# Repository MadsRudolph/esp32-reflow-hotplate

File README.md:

# ESP32 SMD Reflow Hotplate

A from-scratch SMD reflow hotplate built around an ESP32, a 24 V DC PTC heater plate,
and a custom CNC-milled single-sided control board. Designed to reflow small/medium
SMD boards (up to ~100 × 100 mm) using PID-controlled reflow profiles.

> **Status:** in design. See [`docs/`](docs/) for the design spec.

## Why DC PTC (not mains)

The heater runs on **24 V DC**, switched by a power MOSFET — no mains voltage anywhere
in the build. Safer to build, debug, and leave running than an SSR + AC element.

## System overview

| Subsystem | Choice |
|---|---|
| Controller | ESP32 DevKit module |
| Heater | 24 V DC PTC aluminium plate, ~300 W (~13 A) |
| Power switch | IRFS4710 N-MOSFET, 12 V gate drive |
| Temp sensing | K-type thermocouple + MAX31855 (SPI) |
| Logic supply | 24 V → 5 V via LM2576 switching regulator |
| Gate-drive supply | 24 V → 12 V via LM7812 |
| UI | SSD1306 OLED + rotary encoder + start/stop button |
| Control board | Single-sided, through-hole, CNC-milled (Roland SRM-20) |
| Enclosure | 3D-printed (offset electronics box + metal-standoff plate mount) |

Most passives, the MOSFET, regulators, connectors and the encoder come from the **DTU
component shop** (through-hole lab stock). The ESP32 DevKit, MAX31855 thermocouple
module, OLED, 24 V PSU and the PTC heater plate are external modules/hardware.

## Repository layout

```
docs/            design spec, BOM, sourcing notes
hardware/kicad/   KiCad 10 project (schematic + single-sided board)
hardware/3d/      Blender sources + exported STL/STEP for printing
firmware/         ESP32 reflow-control firmware
```

## Production

- **PCB:** CNC-milled on a Roland SRM-20 (FR-1), single-sided, top nets as wire bridges.
  Design rules match the DTU laser/mill process: 1.0 mm trace / 0.8 mm clearance.
- **Enclosure:** FDM 3D print. The hot-plate mount uses **metal standoffs** with an air
  gap from the plastic — the plate reaches ~250 °C and must never touch printed parts.

## Safety

Mains-free by design, but reflow temperatures are dangerous. Planned protections:
hardware gate pulldown (power-off = heater-off), an inline thermal cutoff fuse on the
heater, a fused 24 V input, and firmware thermal-runaway / over-temperature watchdogs.

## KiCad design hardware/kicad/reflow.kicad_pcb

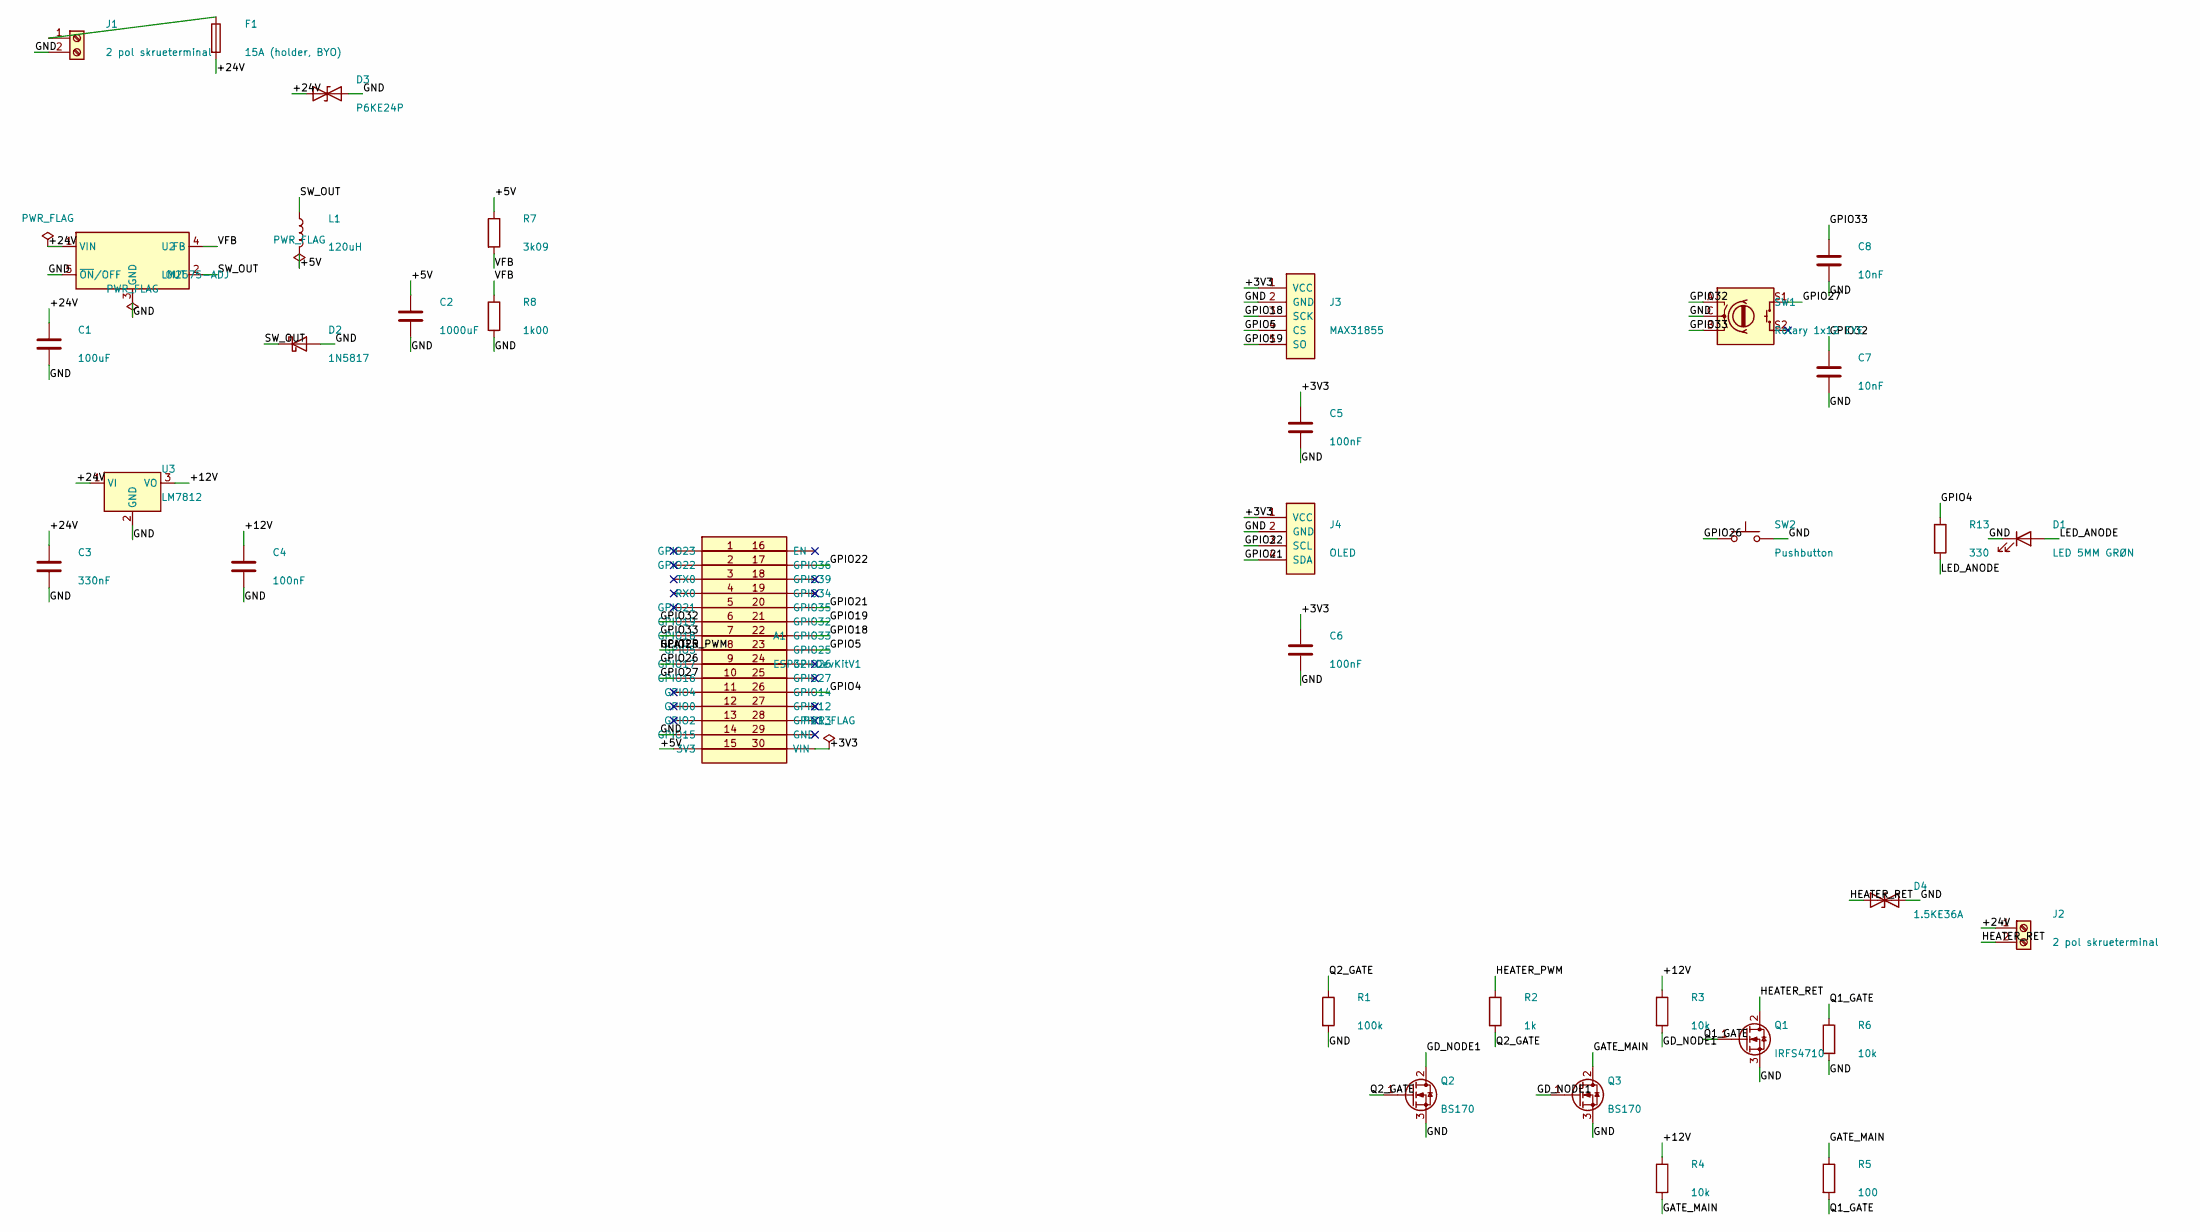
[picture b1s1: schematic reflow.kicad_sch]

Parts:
A1: ESP32-DevKitV1; ESP32_DevKitV1_2x15_P2.54_W22.86
C1: 100uF; CP_Radial_D8.0mm_P3.50mm
C2: 1000uF; CP_Radial_D10.0mm_P5.00mm
C3: 330nF; C_Disc_D5.0mm_W2.5mm_P2.50mm
C4, C5, C6: 100nF; C_Disc_D5.0mm_W2.5mm_P2.50mm
C7, C8: 10nF; C_Disc_D5.0mm_W2.5mm_P2.50mm
D1: LED 5MM GRØN; LED_D5.0mm
D2: 1N5817; D_DO-41_SOD81_P10.16mm_Horizontal
D3: P6KE24P; D_DO-201AD_P15.24mm_Horizontal
D4: 1.5KE36A; D_DO-201AD_P15.24mm_Horizontal
F1: 15A (holder, BYO); Fuseholder_Cylinder-5x20mm_Schurter_FUP_0031.2510_Horizonta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
J1, J2: 2 pol skrueterminal; TerminalBlock_bornier-2_P5.08mm
J3: MAX31855; Header_1x05_P2.54
J4: OLED; Header_1x04_P2.54
L1: 120uH; L_Toroid_Vertical_L26.7mm_W14.0mm_P10.16mm_Pulse_D
Q1: IRFS4710; TO-220-3_Vertical_LaserPads
Q2, Q3: BS170; TO-92_Inline_GDS
R1: 100k; R_Axial_DIN0207_L6.3mm_D2.5mm_P7.62mm_Horizontal
R2: 1k; R_Axial_DIN0207_L6.3mm_D2.5mm_P7.62mm_Horizontal
R3, R4, R6: 10k; R_Axial_DIN0207_L6.3mm_D2.5mm_P7.62mm_Horizontal
R5: 100; R_Axial_DIN0207_L6.3mm_D2.5mm_P7.62mm_Horizontal
R7: 3k09; R_Axial_DIN0207_L6.3mm_D2.5mm_P7.62mm_Horizontal
R8: 1k00; R_Axial_DIN0207_L6.3mm_D2.5mm_P7.62mm_Horizontal
R13: 330; R_Axial_DIN0207_L6.3mm_D2.5mm_P7.62mm_Horizontal
SW1: Rotary 1x12 EYE; RotaryEncoder_Alps_EC11E-Switch_Vertical_H20mm
SW2: Pushbutton; SW_PUSH_6mm
U2: LM2575-ADJ; TO-220-5_Vertical_LaserPads
U3: LM7812; TO-220-3_Vertical_LaserPads

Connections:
/+3V3: A1.30 (3V3), C5.1, C6.1, J3.1 (VCC), J4.1 (VCC)
/+5V: A1.15 (VIN), C2.1, L1.2, R7.1
/+12V: C4.1, R3.1, R4.1, U3.3 (VO)
/+24V: C1.1, C3.1, D3.1 (A1), F1.2, J2.1, U2.1 (VIN), U3.1 (VI)
/GATE_MAIN: Q3.2 (D), R4.2, R5.1
/GD_NODE1: Q2.2 (D), Q3.1 (G), R3.2
/GND: A1.14 (GND), C1.2, C2.2, C3.2, C4.2, C5.2, C6.2, C7.2, C8.2, D1.1 (K), D2.2 (A), D3.2 (A2), D4.2 (A2), J1.2, J3.2 (GND), J4.2 (GND), Q1.3 (S), Q2.3 (S), Q3.3 (S), R1.2, R6.2, R8.2, SW1.C, SW2.2, U2.3 (GND), U2.5 (~ON/OFF), U3.2 (GND)
/GPIO4: A1.26 (GPIO4), R13.1
/GPIO5: A1.23 (GPIO5), J3.4 (CS)
/GPIO18: A1.22 (GPIO18), J3.3 (SCK)
/GPIO19: A1.21 (GPIO19), J3.5 (SO)
/GPIO21: A1.20 (GPIO21), J4.4 (SDA)
/GPIO22: A1.17 (GPIO22), J4.3 (SCL)
/GPIO25: A1.8 (GPIO25), R2.1
/GPIO26: A1.9 (GPIO26), SW2.1
/GPIO27: A1.10 (GPIO27), SW1.S1
/GPIO32: A1.6 (GPIO32), C7.1, SW1.A
/GPIO33: A1.7 (GPIO33), C8.1, SW1.B
/HEATER_RET: D4.1 (A1), J2.2, Q1.2 (D)
/LED_ANODE: D1.2 (A), R13.2
/Q1_GATE: Q1.1 (G), R5.2, R6.1
/Q2_GATE: Q2.1 (G), R1.1, R2.2
/SW_OUT: D2.1 (K), L1.1, U2.2 (OUT)
/VFB: R7.2, R8.1, U2.4 (FB)
unnamed: F1.1, J1.1

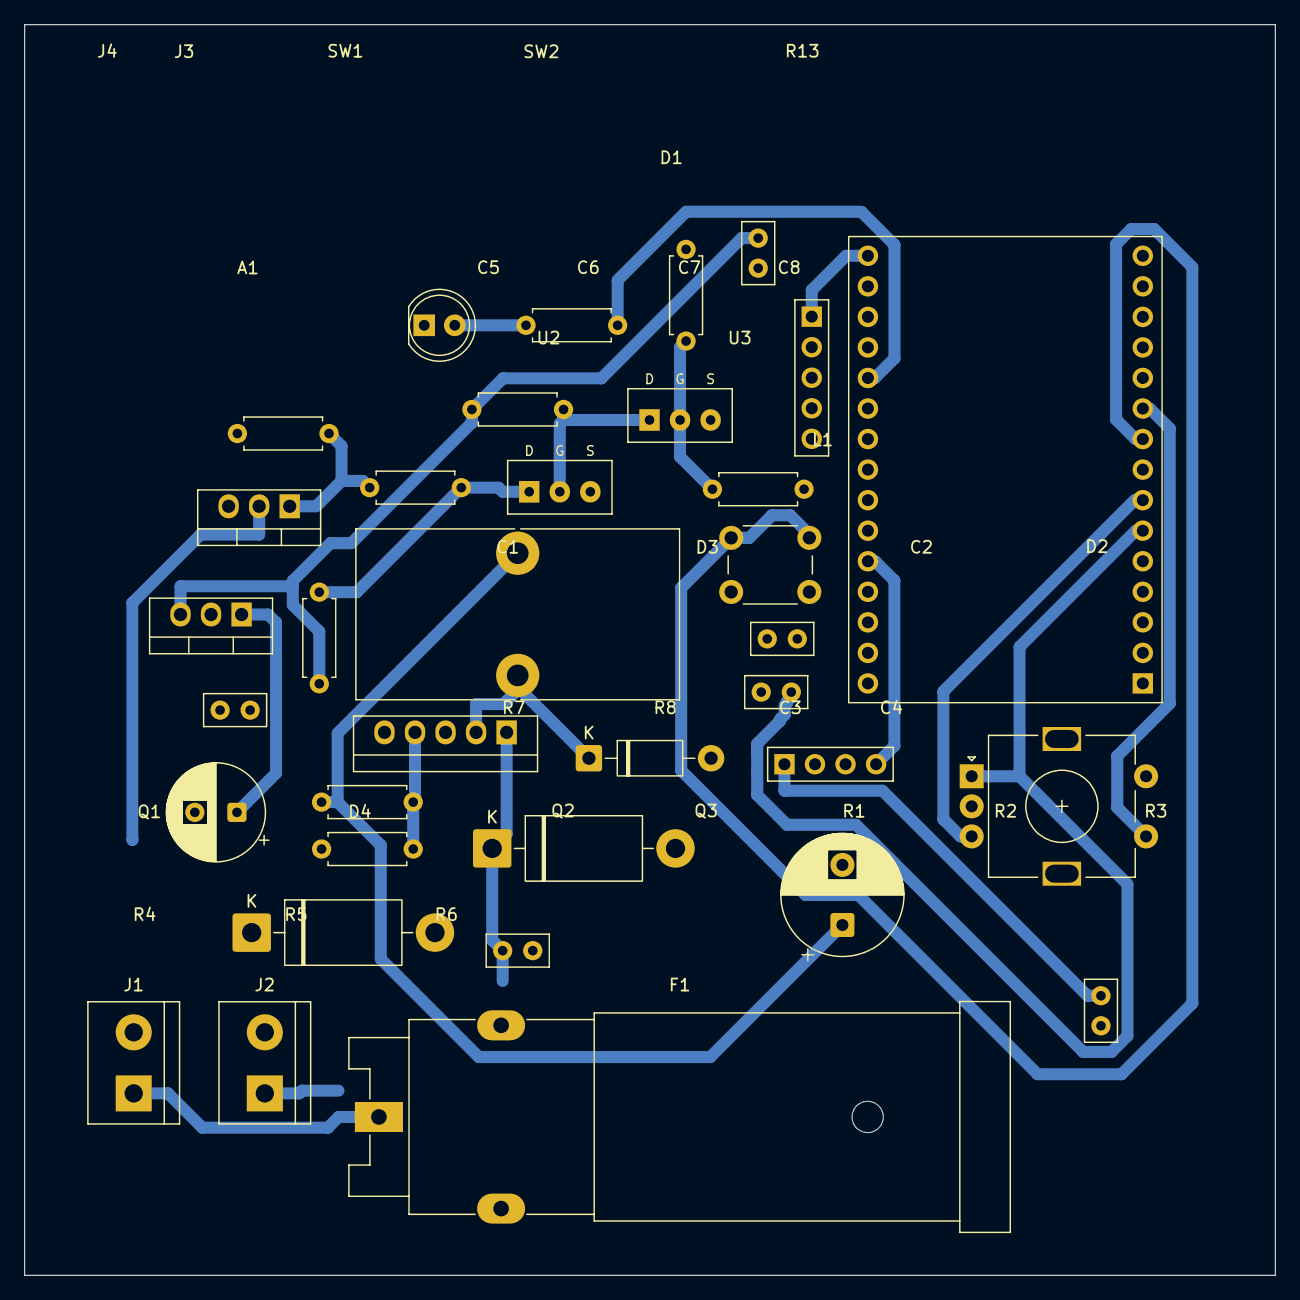
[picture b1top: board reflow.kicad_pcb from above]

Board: 2 copper layers, 104.0 x 104.0 mm, 35 parts (0 on the bottom side), 25 nets.

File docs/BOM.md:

# Bill of Materials — ESP32 reflow hotplate

> Generated from `hardware/kicad/reflow.kicad_sch` (the schematic is
> produced by `hardware/kicad/tools/build_schematic.py`). Every
> **board-soldered** line below resolves to a row in the DTU component
> shop catalogue (`components-inventory/dtu_component_shop(1).csv`),
> verified by `hardware/kicad/tools/check_bom_against_shop.py` (exit 0).
> Modules and bring-your-own hardware are listed separately under
> **External / bring-your-own**.

## Board-soldered parts (DTU component shop)

| Ref | Value | Shop Part_Number | Shop category | Description / role | Footprint |
|---|---|---|---|---|---|
| C1 | 100uF | `100µF` | Capacitor / Electrolytic | Buck input bulk cap, +24V->GND (use >=35V can) | `CP_Radial_D8.0mm_P3.50mm` |
| C2 | 1000uF | `1000µF` | Capacitor / Electrolytic | Buck output cap, +5V->GND (>=16V; 50V shop part) | `CP_Radial_D10.0mm_P5.00mm` |
| C3 | 330nF | `330n` | Capacitor / Film | LM7812 input bypass, +24V->GND | `C_Disc_D5.0mm_W2.5mm_P2.50mm` |
| C4 | 100nF | `100n` | Capacitor / Ceramic | LM7812 output bypass, +12V->GND | `C_Disc_D5.0mm_W2.5mm_P2.50mm` |
| C5 | 100nF | `100n` | Capacitor / Ceramic | MAX31855 (J3) VCC decoupling | `C_Disc_D5.0mm_W2.5mm_P2.50mm` |
| C6 | 100nF | `100n` | Capacitor / Ceramic | OLED (J4) VCC decoupling | `C_Disc_D5.0mm_W2.5mm_P2.50mm` |
| C7 | 10nF | `10n` | Capacitor / Ceramic | Encoder A debounce | `C_Disc_D5.0mm_W2.5mm_P2.50mm` |
| C8 | 10nF | `10n` | Capacitor / Ceramic | Encoder B debounce | `C_Disc_D5.0mm_W2.5mm_P2.50mm` |
| D1 | LED 5MM GRØN | `LED 5MM GRØN` | LED / 5mm | Status LED (GPIO4 via R13) | `LED_D5.0mm` |
| D2 | 1N5817 | `1N5817` | Diode / Schottky | Buck catch diode (Schottky) | `D_DO-41_SOD81_P10.16mm_Horizontal` |
| D3 | P6KE24P | `P6KE24P` | Diode / TVS | 24V input-rail TVS clamp | `D_DO-201AD_P15.24mm_Horizontal` |
| D4 | 1.5KE36A | `1.5KE36A` | Diode / TVS Zener | Heater-drain (HEATER_RET) TVS clamp | `D_DO-201AD_P15.24mm_Horizontal` |
| J1 | 2 pol skrueterminal | `2 pol skrueterminal` | Connector / Terminal | 24V input screw terminal | `TerminalBlock_bornier-2_P5.08mm` |
| J2 | 2 pol skrueterminal | `2 pol skrueterminal` | Connector / Terminal | Heater output screw terminal | `TerminalBlock_bornier-2_P5.08mm` |
| L1 | 120uH | `120µ 1A` | Inductor / Through-hole | Buck inductor (switch node -> +5V) | `L_Toroid_Vertical_L26.7mm_W14.0mm_P10.16mm_Pulse_D` |
| Q1 | IRFS4710 | `IRFS4710` | Transistor / N-MOSFET | Heater low-side power MOSFET | `TO-220-3_Vertical_LaserPads` |
| Q2 | BS170 | `BS170` | Transistor / N-MOSFET | Gate-drive stage-1 level shifter (BS170) | `TO-92_Inline_GDS` |
| Q3 | BS170 | `BS170` | Transistor / N-MOSFET | Gate-drive stage-2 level shifter (BS170) | `TO-92_Inline_GDS` |
| R1 | 100k | `100K` | Resistor / E96 Standard | Q2.G -> GND pulldown (boot-safe) | `R_Axial_DIN0207_L6.3mm_D2.5mm_P7.62mm_Horizontal` |
| R2 | 1k | `1K00` | Resistor / E96 Standard | HEATER_PWM -> Q2.G series | `R_Axial_DIN0207_L6.3mm_D2.5mm_P7.62mm_Horizontal` |
| R3 | 10k | `10K0` | Resistor / E96 Standard | GD_NODE1 -> +12V pull-up | `R_Axial_DIN0207_L6.3mm_D2.5mm_P7.62mm_Horizontal` |
| R4 | 10k | `10K0` | Resistor / E96 Standard | GATE_MAIN -> +12V pull-up | `R_Axial_DIN0207_L6.3mm_D2.5mm_P7.62mm_Horizontal` |
| R5 | 100 | `100R` | Resistor / E96 Standard | GATE_MAIN -> Q1.G series gate resistor | `R_Axial_DIN0207_L6.3mm_D2.5mm_P7.62mm_Horizontal` |
| R6 | 10k | `10K0` | Resistor / E96 Standard | Q1.G -> GND gate-source pulldown | `R_Axial_DIN0207_L6.3mm_D2.5mm_P7.62mm_Horizontal` |
| R7 | 3k09 | `3K09` | Resistor / E96 Standard | LM2575-ADJ FB divider top (+5V->VFB) | `R_Axial_DIN0207_L6.3mm_D2.5mm_P7.62mm_Horizontal` |
| R8 | 1k00 | `1K00` | Resistor / E96 Standard | LM2575-ADJ FB divider bottom (VFB->GND) | `R_Axial_DIN0207_L6.3mm_D2.5mm_P7.62mm_Horizontal` |
| R13 | 330 | `330R` | Resistor / E96 Standard | Status-LED current-limit resistor | `R_Axial_DIN0207_L6.3mm_D2.5mm_P7.62mm_Horizontal` |
| SW1 | Rotary 1x12 EYE | `Rotary 1x12 EYE` | Encoder / Rotary | Rotary encoder (UI) | `RotaryEncoder_Alps_EC11E-Switch_Vertical_H20mm` |
| SW2 | Pushbutton | `Pushbutton` | Hardware / Switch | Start push button (UI) | `SW_PUSH_6mm` |
| U2 | LM2575-ADJ | `LM2575` | IC / Linear | 24V->5V buck regulator (LM2575-ADJ + R7/R8 divider) | `TO-220-5_Vertical_LaserPads` |
| U3 | LM7812 | `LM7812` | IC / Voltage Regulator | 24V->12V linear regulator (gate-drive rail) | `TO-220-3_Vertical_LaserPads` |

### Consolidated purchase list (board parts)

| Qty | Shop Part_Number | Category |
|---|---|---|
| 3 | `100n` | Capacitor/Ceramic |
| 3 | `10K0` | Resistor/E96 Standard |
| 2 | `10n` | Capacitor/Ceramic |
| 2 | `1K00` | Resistor/E96 Standard |
| 2 | `2 pol skrueterminal` | Connector/Terminal |
| 2 | `BS170` | Transistor/N-MOSFET |
| 1 | `1.5KE36A` | Diode/TVS Zener |
| 1 | `1000µF` | Capacitor/Electrolytic |
| 1 | `100K` | Resistor/E96 Standard |
| 1 | `100R` | Resistor/E96 Standard |
| 1 | `100µF` | Capacitor/Electrolytic |
| 1 | `120µ 1A` | Inductor/Through-hole |
| 1 | `1N5817` | Diode/Schottky |
| 1 | `330R` | Resistor/E96 Standard |
| 1 | `330n` | Capacitor/Film |
| 1 | `3K09` | Resistor/E96 Standard |
| 1 | `IRFS4710` | Transistor/N-MOSFET |
| 1 | `LED 5MM GRØN` | LED/5mm |
| 1 | `LM2575` | IC/Linear |
| 1 | `LM7812` | IC/Voltage Regulator |
| 1 | `P6KE24P` | Diode/TVS |
| 1 | `Pushbutton` | Hardware/Switch |
| 1 | `Rotary 1x12 EYE` | Encoder/Rotary |

## External / bring-your-own (not board-soldered shop parts)

| Ref | Part | Description | Note |
|---|---|---|---|
| A1 | ESP32-DevKitV1 | 30-pin DOIT ESP32 DevKit V1 controller module | Hand-soldered 2x15 pin-header module (not a discrete shop part) |
| J3 | MAX31855 | MAX31855 K-type thermocouple amplifier breakout + thermocouple | Module on a 1x05 header; thermocouple is bring-your-own |
| J4 | OLED (SSD1306) | 0.96" SSD1306 128x64 I2C OLED module | Module on a 1x04 header |
| F1 | 24V fuse holder + element | 5x20mm cartridge fuse holder, ~15A fuse element | Fuse holder soldered; the fuse element is user-supplied (bring-your-own) |
| PSU | 24V DC supply | External 24V mains PSU feeding J1 | Bring-your-own; sized for the ~310W heater + logic |
| HTR | PTC hotplate element | 24V PTC heating plate wired to J2 | Bring-your-own heating element (~13A) |
| TF | Inline thermal fuse | Series thermal cutoff on the heater feed | Bring-your-own over-temperature safety cutoff |

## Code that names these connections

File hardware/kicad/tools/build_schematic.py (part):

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    # fixed-5.0 part which tied FB straight to +5V.
    ("+5V", "R7", "1"),     # divider top -> +5V (sensed output)
    ("VFB", "R7", "2"),     # R7 bottom = feedback node
    ("VFB", "U2", "4"),     # LM2575 FB pin senses the divided output
    ("VFB", "R8", "1"),     # R8 top = feedback node
    ("GND", "R8", "2"),     # divider bottom -> GND

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#   HEATER_RET = J2.2 + Q1.D(2) + D4.1
NETS_POWERSTAGE = [
    # ---- Stage 1 inverter (Q2) ----
    ("HEATER_PWM", "R2", "1"),   # gate-drive INPUT side (A1.GPIO25 wired Task 6)
    ("Q2_GATE", "R2", "2"),      # R2 series -> Q2 gate
    ("Q2_GATE", "Q2", "1"),      # Q2 gate
    ("Q2_GATE", "R1", "1"),      # R1 100k pulldown top
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# =============================================================================
#
# Same net-label-on-outward-stub technique as Tasks 4-5. The contract checker
# (net_contract.py) asserts that each pinmap GPIO *name* (e.g. "GPIO18") appears
# as a label in the schematic, so the GPIO name is used directly as the local
# net label and is dropped on BOTH the A1 pin and the matching peripheral pin --
# that makes them one net AND satisfies the contract in a single pass.
#
# ESP32 A1 pin-number map (from modules.kicad_sym ESP32_DevKitV1):
#   VIN=15, GND=14, 3V3=30, GPIO32=6, GPIO33=7, GPIO25=8, GPIO26=9, GPIO27=10,
#   GPIO22=17, GPIO21=20, GPIO19=21, GPIO18=22, GPIO5=23, GPIO4=26.
# J3 MAX31855: VCC=1 GND=2 SCK=3 CS=4 SO=5.
# J4 OLED:     VCC=1 GND=2 SCL=3 SDA=4.
# SW1 RotaryEncoder_Switch: pins A/B/C/S1/S2 (number == letter).
# SW2 SW_Push: 1, 2.   D1 LED: 1=K(cathode), 2=A(anode).
#
# HEATER_PWM: A1.GPIO25 joins the existing HEATER_PWM net (its gate-drive end was
# wired in Task 5). Two labels share the GPIO25 stub node -- "HEATER_PWM" (for
# connectivity to GATEDRV.IN at R2.1) and "GPIO25" (for the contract checker).
#
# LED: A1.GPIO4 --R13(330)--> D1.A(anode); D1.K(cathode) --> GND. The series R13
# means GPIO4 lands on R13.1 (not directly on D1.A); R13.2 -> D1.A is the local
# LED_ANODE net. The contract enumerates LED_STATUS = [A1.GPIO4, D1.A] at the
# interface level; R13 is a passive interconnect (not enumerated), and the
# checker only requires the "GPIO4" label to be present, which it is on A1.GPIO4.
#
# Decoupling: C5 100nF across J3.VCC(+3V3)->GND, C6 100nF across J4.VCC(+3V3)->GND.
# Debounce:   C7 10nF A(GPIO32)->GND, C8 10nF B(GPIO33)->GND.
# No external I2C pull-ups (SSD1306 module has its own); encoder + button use the
# ESP32 internal pull-ups (no external R).
NETS_CTRL = [
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    # ---- MAX31855 thermocouple (J3, SPI) ----
    ("+3V3", "J3", "1"),     # J3.VCC <- +3V3
    ("GND", "J3", "2"),      # J3.GND
    ("GPIO18", "J3", "3"),   # J3.SCK = A1.GPIO18 (TC_SCK)
    ("GPIO5", "J3", "4"),    # J3.CS  = A1.GPIO5  (TC_CS)
    ("GPIO19", "J3", "5"),   # J3.SO  = A1.GPIO19 (TC_SO)
    ("GPIO18", "A1", "22"),  # A1.GPIO18
    ("GPIO5", "A1", "23"),   # A1.GPIO5
    ("GPIO19", "A1", "21"),  # A1.GPIO19

    # ---- OLED (J4, I2C) ----
    ("+3V3", "J4", "1"),     # J4.VCC <- +3V3
    ("GND", "J4", "2"),      # J4.GND
    ("GPIO22", "J4", "3"),   # J4.SCL = A1.GPIO22 (OLED_SCL)
    ("GPIO21", "J4", "4"),   # J4.SDA = A1.GPIO21 (OLED_SDA)
    ("GPIO22", "A1", "17"),  # A1.GPIO22
    ("GPIO21", "A1", "20"),  # A1.GPIO21

    # ---- Rotary encoder (SW1) ----
    ("GPIO32", "SW1", "A"),  # SW1.A = A1.GPIO32 (ENC_A)
    ("GPIO33", "SW1", "B"),  # SW1.B = A1.GPIO33 (ENC_B)
    ("GPIO27", "SW1", "S1"), # SW1.S1 = A1.GPIO27 (ENC_SW)
    ("GND", "SW1", "C"),     # SW1.C common = GND
    ("GPIO32", "A1", "6"),   # A1.GPIO32
    ("GPIO33", "A1", "7"),   # A1.GPIO33
    ("GPIO27", "A1", "10"),  # A1.GPIO27

    # ---- Encoder debounce caps ----
    ("GPIO32", "C7", "1"),   # C7 A->GND debounce, top = ENC_A node
    ("GND", "C7", "2"),
    ("GPIO33", "C8", "1"),   # C8 B->GND debounce, top = ENC_B node
    ("GND", "C8", "2"),

    # ---- Start button (SW2) ----
    ("GPIO26", "SW2", "1"),  # SW2.1 = A1.GPIO26 (BTN_START)
    ("GND", "SW2", "2"),     # SW2.2 = GND
    ("GPIO26", "A1", "9"),   # A1.GPIO26

    # ---- Status LED (D1) via R13 ----
    ("GPIO4", "A1", "26"),   # A1.GPIO4 (LED_STATUS)
    ("GPIO4", "R13", "1"),   # R13.1 = GPIO4 side
    ("LED_ANODE", "R13", "2"),  # R13.2 -> D1 anode (local node)
    ("LED_ANODE", "D1", "2"),   # D1.A (anode) = pin 2
    ("GND", "D1", "1"),         # D1.K (cathode) = pin 1 -> GND

    # ---- Decoupling caps ----
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    ("+3V3", "C6", "1"),     # C6 across J4.VCC->GND
    ("GND", "C6", "2"),

    # ---- Heater PWM logic input (A1.GPIO25 -> existing HEATER_PWM net) ----
    ("HEATER_PWM", "A1", "8"),  # joins GATEDRV.IN (R2.1) wired in Task 5
]

# Extra labels that must share an existing stub node (same ref+pin) without a new
# wire. Used for the GPIO25 pin, which carries the HEATER_PWM net label (above)
# plus a second "GPIO25" label so the contract checker sees the GPIO25 name.
# (net_label, ref, pin)
NETS_CTRL_ALIASES = [
    ("GPIO25", "A1", "8"),
]

# =============================================================================
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    return f'\t(no_connect\n\t\t(at {x} {y})\n\t\t(uuid "{uid()}")\n\t)'


# Net-label visual styling. KiCad treats SW_OUT / J1_HOT as ordinary local nets.
_STUB = 2.54  # mm wire-stub length from the pin endpoint


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    ``NETS_CTRL`` emits a short outward stub from the pin endpoint with a net
    label on its far end; identical label names form one net. ``NETS_CTRL_ALIASES``
    drops an *extra* label on an existing stub-far node (no new wire) -- used so
    the GPIO25 pin carries both "HEATER_PWM" (connectivity) and "GPIO25" (the
    contract checker). The +3V3 PWR_FLAG (in PWR_FLAGS) is emitted by
    render_power_wiring and lands on the same A1.3V3 stub-far node.
    """
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
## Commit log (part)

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2026-06-29 Initialize ESP32 reflow hotplate project repo
2026-06-29 Add reflow hotplate design spec
2026-06-29 Spec: boot-safe non-inverting gate drive + ESP32 pin map
2026-06-29 Add hardware (schematic + board) implementation plan
2026-06-29 hardware: KiCad 10 project skeleton + vendored footprint/symbol libs
2026-06-29 hardware: net contract, pin map, and module symbols/footprints
2026-06-29 hardware: reconcile net contract power tree (drop phantom 3V3 LDO, U2/U3 regs, interface-level GATEDRV block)
2026-06-29 hardware: place all schematic components
2026-06-29 hardware: fix MOSFET lib_id to Device:Q_NMOS_GDS; add U2 footprint TODO
    Change Q1/Q2/Q3 lib_id from Transistor_FET:Q_NMOS_GDS to Device:Q_NMOS_GDS
    (standard KiCad 10 location) in both the PIN_IDS map and COMPONENTS list.
    Add inline TODO on U2 noting the 5-pin LM2576 needs a TO-220-5 laser-pad
    footprint variant before board layout.
    Regenerated reflow.kicad_sch: 37 components, placement check MISSING [],
    kicad-cli export exits 0 with no unresolved-symbol warnings,
2026-06-29 hardware: wire 24V input protection, LM2576 5V, LM7812 12V rails
2026-06-29 hw(buck): swap L1 to 120uH 1A to clear peak-current margin
    The 100uH/0.66A shop inductor was below the calculated LM2576 peak
    inductor current (~0.82-0.88A at 0.5A load). Replace with the DTU
    shop 120uH/1A part: 1A rating exceeds the 0.82A peak with ~20% margin
    and reduces ripple from ~0.76A(pp) to ~0.63A(pp).
    Update electrical-calcs.md with recomputed ripple (0.63A pp) and peak
    (0.82A) for L=120uH, and confirm 1A rating provides adequate margin.
2026-06-29 hardware: wire IRFS4710 power stage with boot-safe two-stage gate drive
    Add NETS_POWERSTAGE wiring pass: two-stage non-inverting BS170 level
    shifter (Q2/Q3) driving the IRFS4710 (Q1) low-side heater switch.
    - R1 100k Q2.G->GND pulldown, R2 1k HEATER_PWM->Q2.G series
    - R3 10k GD_NODE1->+12V pull-up, R4 10k GATE_MAIN->+12V pull-up
    - R5 100R series gate resistor, R6 10k Q1.G->GND gate-source pulldown
    - HEATER_RET = J2.2 = Q1.D; D4 SMBJ33A TVS clamps drain transients
2026-06-29 hardware: wire ESP32, MAX31855 SPI, OLED I2C, encoder, button, status LED
    Add NETS_CTRL pass realising every pinmap GPIO on the ESP32 pins plus the
    J3/J4/SW1/SW2/D1 peripherals and their decoupling/debounce caps. Remove the
    orphaned R7-R12 placeholders (encoder/button use internal pull-ups; OLED has
    its own I2C pull-ups) so the resistor set is R1-R6 + R13. Add +3V3 and +5V
    PWR_FLAGs to give those rails an ERC driver. net_contract now passes; the
    controller section has no unconnected/undriven ERC errors.
2026-06-29 hardware: assign footprints, ERC clean, finalize electrical calcs
    - Q2/Q3 (BS170): new energy_system:TO-92_Inline_GDS footprint with NUMERIC
    pads 1/2/3 placed at the BS170 physical legs (left=Drain, mid=Gate,
    right=Source per ON Semi BS170/D Rev2). Numeric pads are required because
    the stock Q_NMOS_GDS symbol numbers its pins 1/2/3; pcb_build.py and KiCad
    both bind pad-name to pin-number, so G/D/S-named pads would get no net.
    - Q1 (IRFS4710): switch to plain numeric TO-220-3_Vertical_LaserPads (the
2026-06-29 hw(safety): resolve gate PWM-input net by topology in boot-safe check
    The check script was looking up the PWM-input net by the literal label
    "HEATER_PWM", which broke after GPIO25 and HEATER_PWM were merged onto
    one net (KiCad picks "GPIO25" as the primary name in the export).
    Fix: identify the PWM-input net by pin membership — the net containing
    R2 pin 1 (source side of the series gate resistor into Q2.G) — using
    the existing node_net() helper. All boot-safety assertions are unchanged;
2026-06-29 hw(buck): swap U2 to LM2575-ADJ with 5.03V feedback divider (R7 3K09 / R8 1K00)
    The DTU component shop stocks the adjustable LM2575, not the fixed LM2576-5.0.
    Swap U2 to LM2575BT-ADJ (same 5-pin TO-220 pinout/footprint) and add an R7/R8
    feedback divider into FB: Vout = 1.23*(1+3090/1000) = 5.03 V. Also fold the
    post-placement footprint finalization (5-pin laser pads, GDS variants, real
    toroid, fuse holder) and the unused-pin no_connect markers into build_schematic
    so it regenerates the finalized schematic faithfully. ERC=0, pad-nets and
2026-06-29 hardware: BOM generated and cross-checked against DTU component shop
    Add check_bom_against_shop.py: reads board-soldered parts from the netlist
    (excludes A1/J3/J4 modules + F1 fuse holder), normalises each value (µ/u, Ω/R,
    k/K, E96 codes, cap/diode formats) and asserts a Part_Number/Value match in
    dtu_component_shop(1).csv. Exit 0 = all resolve.
    Snap the parts that only differed by value-string formatting to shop stock:
    D3 24V-rail TVS -> P6KE24P (24V standoff, ~33V clamp < 35V caps), D4 drain TVS
2026-06-29 hw(erc): restore C6 labels to script-computed pin endpoints; ERC back to 0
    The schematic was re-saved by KiCad (version stamp 20250114 → 20260306),
    which drifted the C6 +3V3 and GND net labels +0.064 mm in X and -0.114 mm
    in Y off the wire stub endpoints, leaving both labels dangling and both C6
    pins unconnected (4 ERC errors).
    Regenerated from build_schematic.py — no script changes needed; the script
    already computed the correct coincident coordinates for C6 (same as C5).
2026-06-29 hardware: build board, zone the layout, add high-current pours
    Build the single-sided B.Cu board from the final schematic and place all 35
    footprints into three zones inside the 104x104 mm outline: UI + the analog
    MAX31855 header along the top edge, the ESP32 controller in the centre, and the
    power corner (24V input, both regulators, buck passives, FB divider, heater
    MOSFET + gate drive, screw terminals + fuse) bottom-left - keeping the analog
    header far from the heater MOSFET.
2026-06-29 hardware: two-stage route (165 B.Cu tracks + 86 F.Cu jumper segs); 4 connections need manual finish
2026-06-29 hardware: close +3V3 on B.Cu; +24V/HEATER_RET need wire bridges
    Route A1.30 (/+3V3) to the +3V3 net with a 6-segment B.Cu track down the
    clear lane between the ESP module pin column and the buck input, landing on
    the existing +3V3 copper. Refill zones. DRC: 0 copper-rule violations, +3V3
    connected.
    The two high-current crossings (+24V buck-input rail to its pour/F1.2, and
    HEATER_RET upper pads to the lower pour island) cannot be closed on the
2026-06-29 hardware: export SRM-20 mill production files and milling notes
    - B.Cu+Edge DXF (reflow.dxf), F.Cu+Edge DXF (reflow_top_cu.dxf already
    tracked), silk DXF (reflow_silk_top.dxf) via export_production.ps1
    - Mirrored B.Cu SVG (reflow_mill_bcu.svg) for mods CE / gerber2rml
    - Full Gerber set + Excellon drill in production/gerbers/
    - MILL_NOTES.md: three SRM-20 jobs, origin/Z-zero procedure, wide-pour
    caveat, and hand-finish items (86 F.Cu jumpers + 2x 13A wire bridges)
2026-06-29 chore: gitignore freerouting logs and routing scratch
2026-06-29 Add 3D enclosure design spec
2026-06-29 Add 3D enclosure implementation plan
2026-06-29 3d: parametric params + bpy verification harness (manifold/bbox/export)
2026-06-29 3d: parametric plate frame with ceramic-standoff bosses and air gap
2026-06-29 3d: electronics box with PCB bosses, vents, terminal openings, insert bosses
2026-06-29 3d: correct enclosure to 3-part top-panel design (box fits 104x104 board on posts; panel=lid)
2026-06-29 3d: electronics box sized for the board, corner support posts, vents, terminal openings, top-rim inserts
2026-06-29 3d: top control panel with cut-outs from placement.json, mates the box rim
2026-06-29 refactor(panel): read vent anchors from placement.json; assert J4 rotation
    - Vent slot centres now derived from placement.json U2/U3 entries via
    _affine(), replacing hardcoded literals 42.5 / 58.4. Fallback defaults
    preserved so build never crashes if a key is absent.
    - Assert added before OLED boolean that J4 rotation == 0; message explains
    swap needed for 90°/270° orientation.
    Verified: manifold_ok True, fits_bed True, cut_centers unchanged,
2026-06-29 3d: assembly interference check, STL exports, enclosure.blend, and build README
2026-06-29 fix(panel): reposition OLED window fully inside panel; add outline guard
    The OLED window was centred on J4's board coordinate (-46.2, -42.4),
    placing its left edge at -59.2 mm — 2.7 mm past the 56.5 mm panel
    half-width, creating an open-sided notch.
    The SSD1306 module is wired to J4 via cable, so the window position is
    independent of the J4 footprint. Move window to (-25.0, 20.0) — upper-
    left quadrant — with all four edges well within ±53.5 mm (≥15.5 mm
2026-06-29 3d: refresh enclosure.blend and STL exports after OLED window fix
2026-06-29 chore: ignore KiCad autoplace/routing scratch and stray blend
2026-06-30 3d: refit enclosure to re-placed PCB; import board GLB into assembled view; raise box to 40mm for vertical TO-220s
2026-06-30 3d: fix board centering in assembly via origin_set (was offset +60mm in X)
2026-06-30 hardware: update board with re-placed footprints (user re-placement)
2026-06-30 Add firmware design spec (ESP-IDF/C, PID, NVS profiles, WiFi dashboard)
2026-06-30 Add firmware Phase 1 (core logic) implementation plan
2026-06-30 firmware: PlatformIO scaffold with native Unity test env
2026-06-30 firmware/core: PID with anti-windup and derivative-on-measurement
2026-06-30 safety(pid): guard dt=0 derivative and add NaN/Inf output clamp
    - Skip derivative (and avoid divide-by-zero) when dt_s <= 0
    - After computing output, force to out_min if isnan/isinf — fail-safe
    - Two new regression tests: test_dt_zero_is_finite_and_safe, test_output_never_nan
2026-06-30 firmware/core: reflow profile model, interpolation, validation, defaults
2026-06-30 firmware/core: profile settings store with injected storage + seeding
2026-06-30 design: add 5V cooling fan in split-range PID loop (FAN_PWM=GPIO13); core/actuator task + board-revision note
2026-06-30 firmware/core: reflow run state machine with fault/abort transitions
2026-06-30 fix(firmware/core): make reflow abort durable across ticks (latched cooldown)
2026-06-30 firmware/core: safety watchdog (overtemp/runaway/tc-fault/stall)
2026-06-30 fix(firmware/core): defer runaway eval past baseline tick; cover big-dt edges
2026-06-30 firmware/core: split-range actuator (heater/fan deadband mapping)
2026-06-30 firmware: document FAN_PWM=GPIO13 in README pin map (match net contract)
